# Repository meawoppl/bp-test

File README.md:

# PCB workspace

Choose a board in the portal using the selector configured in [`.kicad-pcb.json`](.kicad-pcb.json).

**Moved out (2026-10-20):**

- The ESP32 + iCE40 "gumstick" module (v1 DF40 module, v2 M.2 draft) and its
  programming carrier now live in **[OrbitalCommons/gumstick](https://github.com/OrbitalCommons/gumstick)**
  (public, history preserved; v1 ordered files under Git tag `v1`). Start with the
  [v1 ICD](https://github.com/OrbitalCommons/gumstick/blob/main/current-df40-connectors/docs/ICD-v1.md).
  It is included here as the submodule `third_party/gumstick`
  (`git submodule update --init`) because the Tesla controller scripts read the carrier.
- The GPS time calibrator, now named **StratumZero** (board, case, firmware,
  gateware, validation plan), lives in **[OrbitalCommons/stratumzero](https://github.com/OrbitalCommons/stratumzero)**
  (private for now).

Boards here:

- [Tesla coil controller](boards/tesla-coil-controller/README.md).
- [Original MainBoard](boards/mainboard-reference): native KiCad import for reference; original Fusion/Eagle exports in [source/fusion](source/fusion).
- Direction LED tester: existing board and fabrication files described below.

# Direction LED Differential Input Test Board

A compact 5 V BNC polarity indicator and Backplane workflow test project.

## Revision C

The schematic, 32 × 20 mm PCB, and fabrication files now match. The board is
73% smaller than the original 75 × 32 mm layout. The BNC body sits at the
left edge with its barrel overhanging, and the two indicators sit together on
the right. All routing is on top copper, with no vias.

- D1 / `+` (green 1206) lights when the BNC center is positive relative to its shell.
- D2 / `-` (red 1206) lights when the center is negative relative to its shell.
- A shared 1 kOhm 0805 resistor feeds directly antiparallel LEDs, limiting current
  and allowing the conducting LED to limit reverse voltage across the other.

There are four components: J1, R1, D1, and D2. R2 is removed.

[Layout drawing](docs/layout-review.svg) · [3D view](docs/layout-3d.png) ·
[Schematic](docs/schematic-review.svg)

## Verification and ordering

KiCad 10.0.6 ERC: **0 violations**. DRC with schematic parity: **0 violations,
0 unconnected items, 0 parity issues**, under the current project settings.
Gerbers, drills, BOM, and placements have been regenerated for revision C.

The package is ready for fabrication/assembly review, not an already approved
order. Confirm JLCPCB stock, through-hole assembly of J1, and LED rotation in
the assembly preview. No physical prototype has been tested. See the
[manufacturing notes](docs/manufacturing-notes.md) and [fabrication package](fab/README.md).

## Project files

| File or directory | Purpose |
| --- | --- |
| `direction-led-tester.kicad_pro` | KiCad project settings |
| `direction-led-tester.kicad_sch` | Revision C schematic |
| `direction-led-tester.kicad_pcb` | Revision C, 32 × 20 mm board |
| `bp-test.kicad_sym` | Vendored KiCad resistor and LED symbols |
| `fp-lib-table`, `sym-lib-table` | Project-local library mappings |
| `Resistor_SMD.pretty/`, `LED_SMD.pretty/` | Local KiCad footprints |
| `3dmodels/` | Resistor and LED STEP models |
| `lcsc/` | BNC symbol, corrected footprint, and STEP/WRL source models |
| `fab/` | Revision C fabrication, assembly, and check outputs |

The [workflow log](docs/plugin-workflow-log.md) records plugin testing and prior
revisions; use the current manufacturing notes for ordering requirements.

## Tesla coil controller

[Acquisition-first controller development](boards/tesla-coil-controller/README.md): eight simultaneous ADC channels, module v1 carrier interface, and two routed UD2.7-derived GDT bridges. This is an unfinished development board, not a fabrication release.

## License

[MIT](LICENSE). Third-party datasheets, vendor 3D models and imported library
files included for reference keep their own terms; see
`NOTICE`.

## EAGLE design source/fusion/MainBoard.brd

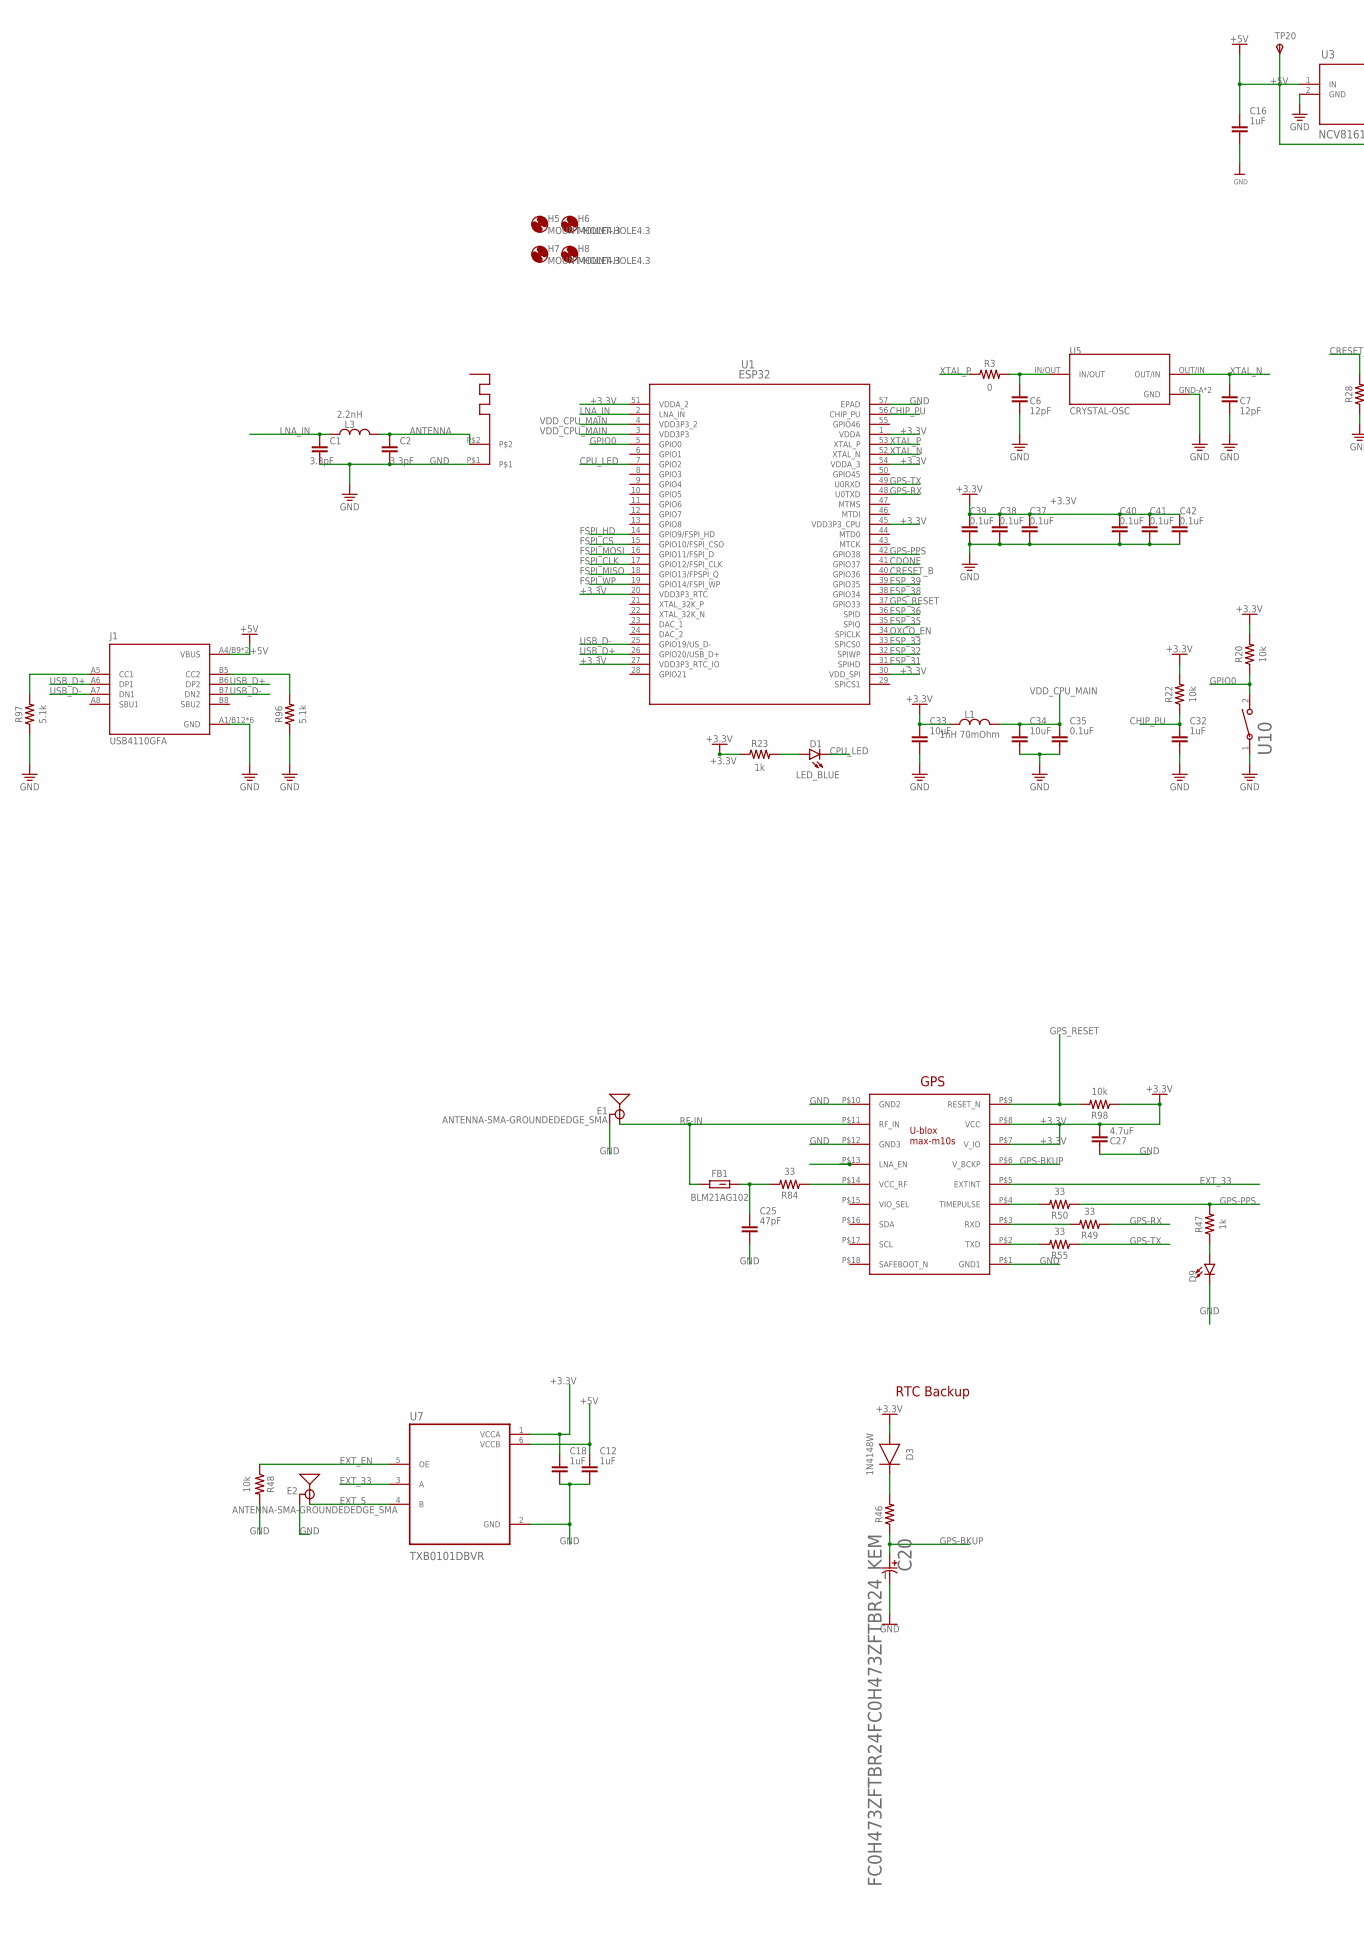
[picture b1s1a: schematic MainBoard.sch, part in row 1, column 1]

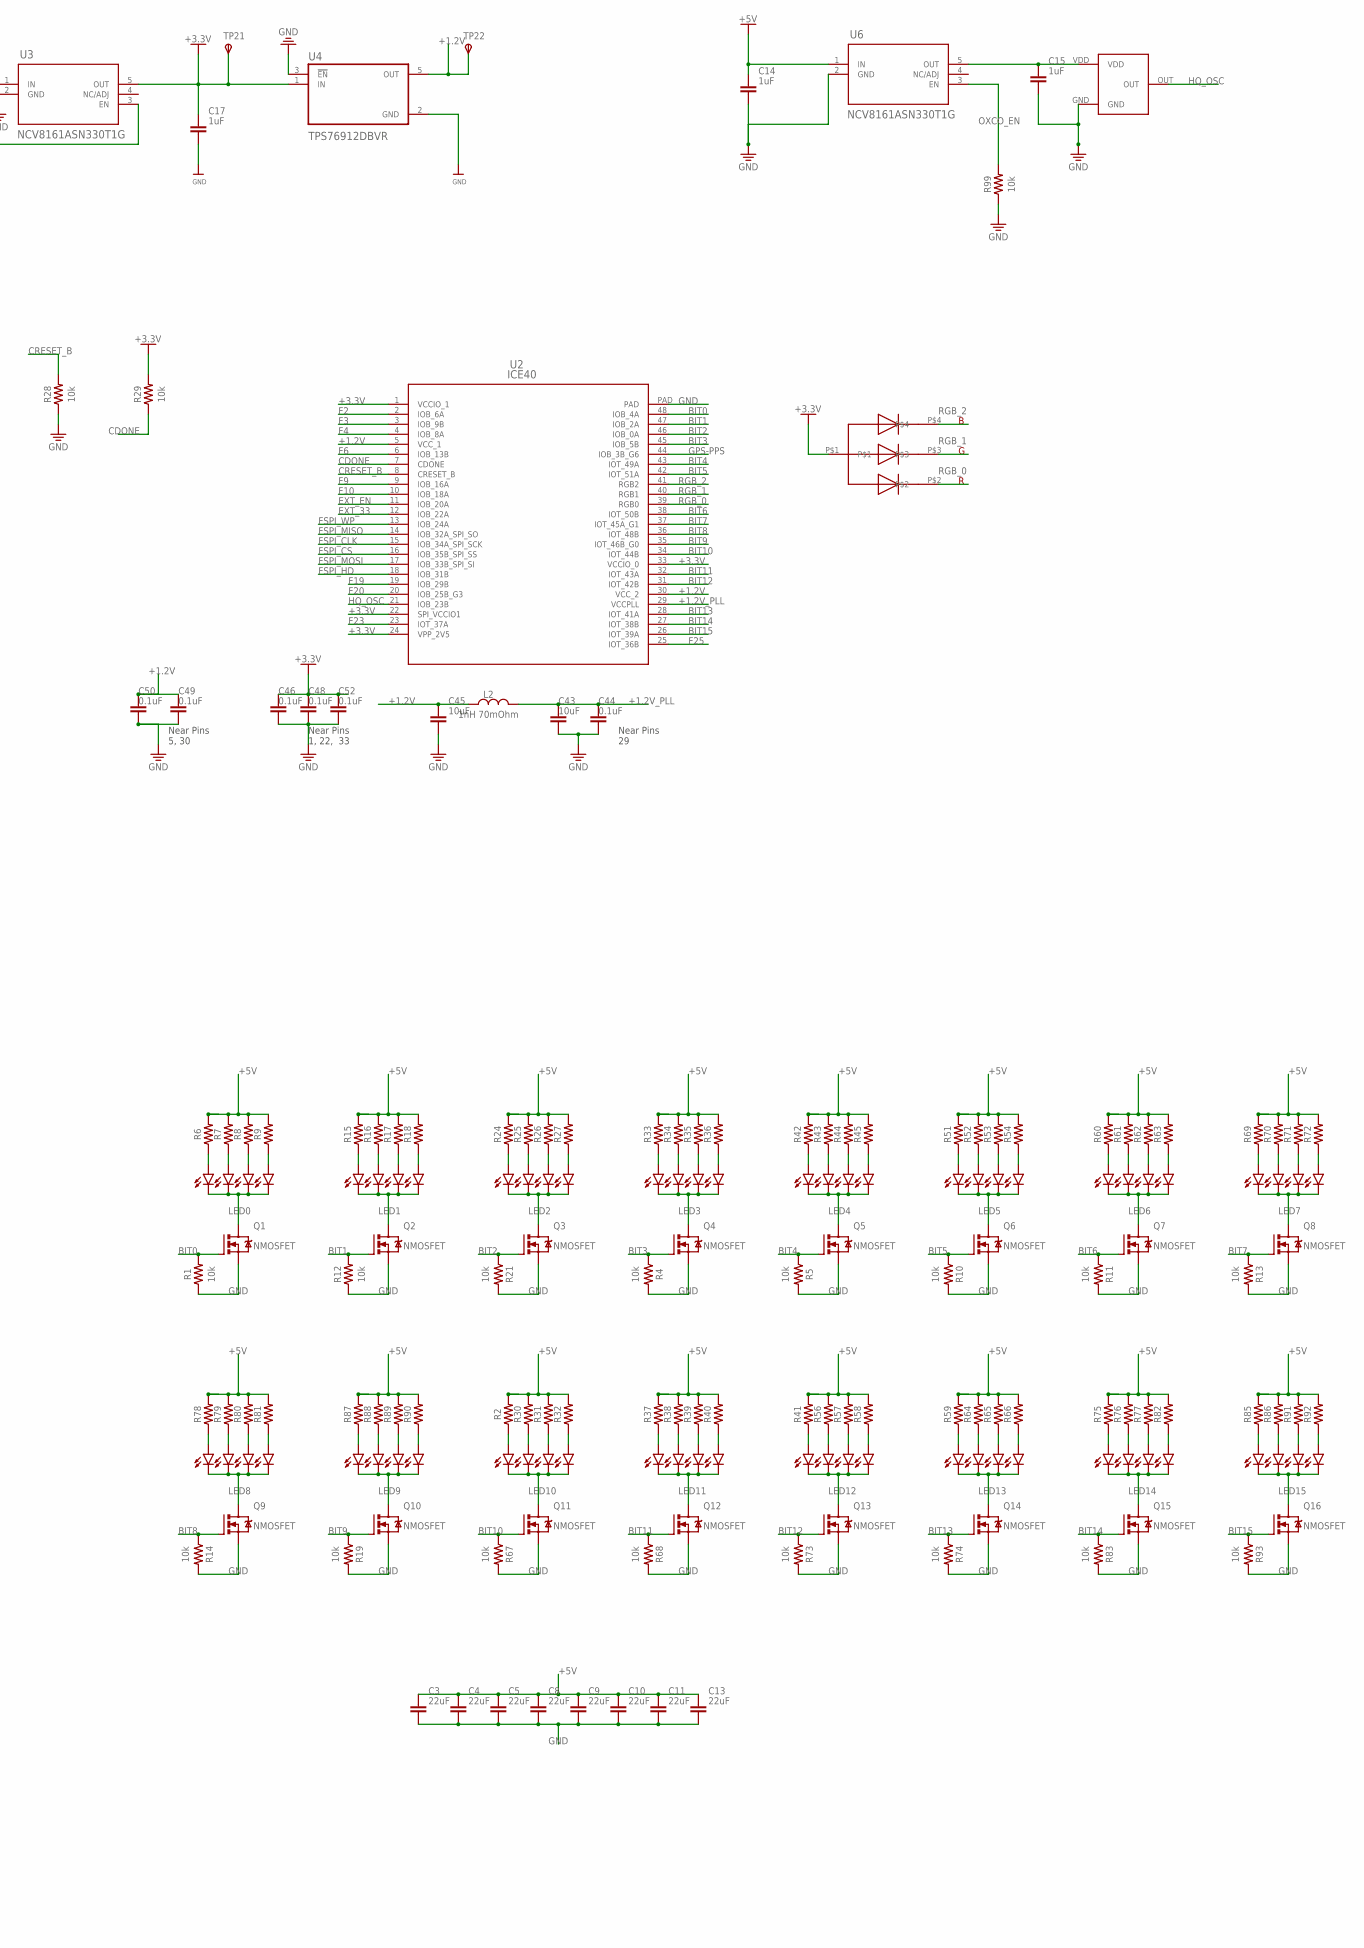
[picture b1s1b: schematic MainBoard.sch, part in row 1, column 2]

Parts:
C1, C2: 3.3pF; CAPC1005X60; LCSC_PART C76906
C3, C4, C5, C8, C9, C10, C11, C13: 22uF; CAPC3225X135; LCSC_PART C52306
C6, C7: 12pF; CAPC1005X60; LCSC_PART C26406
C12, C18, C32: 1uF; CAPC1005X60; LCSC_PART C29266
C14, C15, C16, C17: 1uF; CAPC2012X110; LCSC C28323
C20: FC0H473ZFTBR24FC0H473ZFTBR24_KEM; FC0H473ZFTBR24_KEM
C25: 47pF; CAPC1005X60; LCSC_PART C1671
C27: 4.7uF; CAPC1005X60; LCSC_PART C23733
C33, C34, C43, C45: 10uF; CAPC1005X60; LCSC_PART C76991
C35, C37, C38, C39, C40, C41, C42, C44, C46, C48, C49, C50, C52: 0.1uF; CAPC1005X60; LCSC_PART C1525
D1: LED_BLUE; LEDC1005X25N_FLAT-B; LCSC_PART C22355736
D2, D5, D6, D7, D8, D10, D11, D12, D13, D14, D15, D16, D17, D18, D19, D20, D21, D22, D23, D24, D25, D26, D27, D28, D29, D30, D31, D32, D33, D34, D35, D36, D37, D38, D39, D40, D41, D42, D43, D44, D45, D46, D47, D48, D49, D50, D51, D52, D53, D54, D55, D60, D61, D62, D63, D68, D69, D70, D71, D76, D77, D78, D79: LED_BLUE; LEDC3216X180N_RND-B
D3: 1N4148W; SOD3715X135; LCSC_PART C2128
D4: LED_BLUE; LEDC3216X180N_RND-B; LCSC_PART C375482
D9: LED0603; LED-0603; LCSC_PART C2286
E1, E2: ANTENNA-SMA-GROUNDEDEDGE_SMA; SMA-EDGE
FB1: BLM21AG102; BEADC2012X105N; LCSC_PART C76817
H5, H6, H7, H8: MOUNT-HOLE4.3; 4,3
J1: USB4110GFA; GCT_USB4110GFA; LCSC_PART C34260841
L1, L2: 1nH 70mOhm; INDC1006X60N; LCSC_PART C18222
L3: 2.2nH; INDC1006X60N; LCSC_PART C86061
Q1, Q2, Q3, Q4, Q5, Q6, Q7, Q8, Q9, Q10, Q11, Q12, Q13, Q14, Q15, Q16: NMOSFET; SOT23; LCSC_PART C478010
R1, R4, R5, R10, R11, R12, R13, R14, R19, R21, R67, R68, R73, R74, R83, R93: 10k; RESC2012X65; LCSC_PART C60490
R2, R6, R7, R8, R9, R15, R16, R17, R18, R24, R25, R26, R27, R30, R31, R32, R33, R34, R35, R36, R37, R38, R39, R40, R41, R42, R43, R44, R45, R46, R51, R52, R53, R54, R56, R57, R58, R59, R60, R61, R62, R63, R64, R65, R66, R69, R70, R71, R72, R75, R76, R77, R78, R79, R80, R81, R82, R85, R86, R87, R88, R89, R90, R91, R92: R-US_CHIP-0805(2012-METRIC); RESC2012X65
R3: 0; RESC1005X40; LCSC_PART C17168
R20, R22, R28, R29, R48, R98, R99: 10k; RESC1005X40; LCSC_PART C60490
R23, R47: 1k; RESC1005X40; LCSC_PART C11702
R49, R50, R55, R84: 33; RESC1005X40; LCSC_PART C25105
R96, R97: 5.1k; RESC1005X40; LCSC_PART C25905
TP20, TP22: TPSB1,27; B1,27
TP21: TPSB1,27; B1,27; LCSC DNP
U1: ESP32; QFN56_ESP32-S2FH4_EXP-M
U2: ICE40; ICE40-QFN
U3, U6: NCV8161ASN330T1G; TSOP5_3X1P5_ONS-M
U4: TPS76912DBVR
U5: CRYSTAL-OSC; XTAL_ECS-400-10-36-CKY-TR
U7: TXB0101DBVR; SOT95P280X145-6N; LCSC C2652944
U9: RGBLED
U10: TS-1185-C-A-A-A; SW_CS1213AGF260_CRS
U11: MAX-M10S-00B
U$1: PCB-ANTENNA
U$2: ACO97

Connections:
+1.2V: C45.1, C49.1, C50.1, L2.1, TP22.TP, U2.5 (VCC_1), U2.30 (VCC_2), U4.5 (OUT)
+1.2V_PLL: C43.1, C44.1, L2.2, U2.29 (VCCPLL)
+3.3V: C17.1, C18.1, C27.1, C33.1, C37.1, C38.1, C39.1, C40.1, C41.1, C42.1, C46.1, C48.1, C52.1, D3.2 (A), L1.1, R20.2, R22.2, R23.1, R29.2, R98.1, TP21.TP, U1.1 (VDDA), U1.20 (VDD3P3_RTC), U1.27 (VDD3P3_RTC_IO), U1.30 (VDD_SPI), U1.45 (VDD3P3_CPU), U1.51 (VDDA_2), U1.54 (VDDA_3), U2.1 (VCCIO_1), U2.22 (SPI_VCCIO1), U2.24 (VPP_2V5), U2.33 (VCCIO_0), U3.5 (OUT), U4.1 (IN), U7.1 (VCCA), U9.P$1, U11.P$7 (V_IO), U11.P$8 (VCC)
+5V: C3.1, C4.1, C5.1, C8.1, C9.1, C10.1, C11.1, C12.1, C13.1, C14.1, C16.1, J1.A4/B9 (VBUS), J1.B4/A9 (VBUS), R2.2, R6.2, R7.2, R8.2, R9.2, R15.2, R16.2, R17.2, R18.2, R24.2, R25.2, R26.2, R27.2, R30.2, R31.2, R32.2, R33.2, R34.2, R35.2, R36.2, R37.2, R38.2, R39.2, R40.2, R41.2, R42.2, R43.2, R44.2, R45.2, R51.2, R52.2, R53.2, R54.2, R56.2, R57.2, R58.2, R59.2, R60.2, R61.2, R62.2, R63.2, R64.2, R65.2, R66.2, R69.2, R70.2, R71.2, R72.2, R75.2, R76.2, R77.2, R78.2, R79.2, R80.2, R81.2, R82.2, R85.2, R86.2, R87.2, R88.2, R89.2, R90.2, R91.2, R92.2, TP20.TP, U3.1 (IN), U3.3 (EN), U6.1 (IN), U7.6 (VCCB)
ANTENNA: C2.1, L3.2, U$1.P$2
BIT0: Q1.1 (G), R1.2, U2.48 (IOB_4A)
BIT1: Q2.1 (G), R12.2, U2.47 (IOB_2A)
BIT2: Q3.1 (G), R21.1, U2.46 (IOB_0A)
BIT3: Q4.1 (G), R4.1, U2.45 (IOB_5B)
BIT4: Q5.1 (G), R5.1, U2.43 (IOT_49A)
BIT5: Q6.1 (G), R10.1, U2.42 (IOT_51A)
BIT6: Q7.1 (G), R11.1, U2.38 (IOT_50B)
BIT7: Q8.1 (G), R13.1, U2.37 (IOT_45A_G1)
BIT8: Q9.1 (G), R14.1, U2.36 (IOT_48B)
BIT9: Q10.1 (G), R19.1, U2.35 (IOT_46B_G0)
BIT10: Q11.1 (G), R67.1, U2.34 (IOT_44B)
BIT11: Q12.1 (G), R68.1, U2.32 (IOT_43A)
BIT12: Q13.1 (G), R73.1, U2.31 (IOT_42B)
BIT13: Q14.1 (G), R74.1, U2.28 (IOT_41A)
BIT14: Q15.1 (G), R83.1, U2.27 (IOT_38B)
BIT15: Q16.1 (G), R93.1, U2.26 (IOT_39A)
CDONE: R29.1, U1.41 (GPIO37), U2.7 (CDONE)
CHIP_PU: C32.1, R22.1, U1.56 (CHIP_PU)
CPU_LED: D1.C, U1.7 (GPIO2)
CRESET_B: R28.2, U1.40 (GPIO36), U2.8 (CRESET_B)
ESP_31: U1.31 (SPIHD)
ESP_32: U1.32 (SPIWP)
ESP_33: U1.33 (SPICS0)
ESP_35: U1.35 (SPIQ)
ESP_36: U1.36 (SPID)
ESP_38: U1.38 (GPIO34)
ESP_39: U1.39 (GPIO35)
EXT_5: E2.SIG (SIGNAL), U7.4 (B)
EXT_33: U2.12 (IOB_22A), U7.3 (A), U11.P$5 (EXTINT)
EXT_EN: R48.1, U2.11 (IOB_20A), U7.5 (OE)
F2: U2.2 (IOB_6A)
F3: U2.3 (IOB_9B)
F4: U2.4 (IOB_8A)
F6: U2.6 (IOB_13B)
F9: U2.9 (IOB_16A)
F10: U2.10 (IOB_18A)
F19: U2.19 (IOB_29B)
F20: U2.20 (IOB_25B_G3)
F23: U2.23 (IOT_37A)
F25: U2.25 (IOT_36B)
FSPI_CLK: U1.17 (GPIO12/FSPI_CLK), U2.15 (IOB_34A_SPI_SCK)
FSPI_CS: U1.15 (GPIO10/FSPI_CSO), U2.16 (IOB_35B_SPI_SS)
FSPI_HD: U1.14 (GPIO9/FSPI_HD), U2.18 (IOB_31B)
FSPI_MISO: U1.18 (GPIO13/FPSPI_Q), U2.14 (IOB_32A_SPI_SO)
FSPI_MOSI: U1.16 (GPIO11/FSPI_D), U2.17 (IOB_33B_SPI_SI)
FSPI_WP: U1.19 (GPIO14/FSPI_WP), U2.13 (IOB_24A)
GND: C1.2, C2.2, C3.2, C4.2, C5.2, C6.2, C7.2, C8.2, C9.2, C10.2, C11.2, C12.2, C13.2, C14.2, C15.2, C16.2, C17.2, C18.2, C20.2, C25.2, C27.2, C32.2, C33.2, C34.2, C35.2, C37.2, C38.2, C39.2, C40.2, C41.2, C42.2, C43.2, C44.2, C45.2, C46.2, C48.2, C49.2, C50.2, C52.2, D9.C, E1.GND@0 (GND), E1.GND@1 (GND), E1.GND@2 (GND), E1.GND@3 (GND), E2.GND@0 (GND), E2.GND@1 (GND), E2.GND@2 (GND), E2.GND@3 (GND), J1.A1/B12 (GND), J1.B1/A12 (GND), J1.S1 (GND), J1.S2 (GND), J1.S3 (GND), J1.S4 (GND), Q1.2 (S), Q2.2 (S), Q3.2 (S), Q4.2 (S), Q5.2 (S), Q6.2 (S), Q7.2 (S), Q8.2 (S), Q9.2 (S), Q10.2 (S), Q11.2 (S), Q12.2 (S), Q13.2 (S), Q14.2 (S), Q15.2 (S), Q16.2 (S), R1.1, R4.2, R5.2, R10.2, R11.2, R12.1, R13.2, R14.2, R19.2, R21.2, R28.1, R48.2, R67.2, R68.2, R73.2, R74.2, R83.2, R93.2, R96.1, R97.1, R99.1, U1.57 (EPAD), U2.PAD, U3.2 (GND), U4.2 (GND), U4.3 (!EN), U5.GND-A (GND), U5.GND-B (GND), U6.2 (GND), U7.2 (GND), U10.1, U11.P$1 (GND1), U11.P$10 (GND2), U11.P$12 (GND3), U$1.P$1, U$2.GND
GPIO0: R20.1, U1.5 (GPIO0), U10.2
GPS-BKUP: C20.1, R46.1, U11.P$6 (V_BCKP)
GPS-PPS: R47.2, R50.1, U1.42 (GPIO38), U2.44 (IOB_3B_G6)
GPS-RX: R49.1, U1.48 (U0TXD)
GPS-TX: R55.1, U1.49 (U0RXD)
GPS_RESET: R98.2, U1.37 (GPIO33), U11.P$9 (RESET_N)
HQ_OSC: U2.21 (IOB_23B), U$2.OUT
LED0: D4.C, D5.C, D6.C, D7.C, Q1.3 (D)
LED1: D12.C, D13.C, D14.C, D15.C, Q2.3 (D)
LED2: D20.C, D21.C, D22.C, D23.C, Q3.3 (D)
LED3: D28.C, D29.C, D30.C, D31.C, Q4.3 (D)
LED4: D36.C, D37.C, D38.C, D39.C, Q5.3 (D)
LED5: D44.C, D45.C, D46.C, D47.C, Q6.3 (D)
LED6: D52.C, D53.C, D54.C, D55.C, Q7.3 (D)
LED7: D60.C, D61.C, D62.C, D63.C, Q8.3 (D)
LED8: D68.C, D69.C, D70.C, D71.C, Q9.3 (D)
LED9: D76.C, D77.C, D78.C, D79.C, Q10.3 (D)
LED10: D2.C, D8.C, D10.C, D11.C, Q11.3 (D)
LED11: D16.C, D17.C, D18.C, D19.C, Q12.3 (D)
LED12: D24.C, D25.C, D26.C, D27.C, Q13.3 (D)
LED13: D32.C, D33.C, D34.C, D35.C, Q14.3 (D)
LED14: D40.C, D41.C, D42.C, D43.C, Q15.3 (D)
LED15: D48.C, D49.C, D50.C, D51.C, Q16.3 (D)
LNA_IN: C1.1, L3.1, U1.2 (LNA_IN)
unnamed: D2.A, R2.1
unnamed: C6.1, R3.2, U5.IN/OUT
unnamed: D1.A, R23.2
unnamed: D8.A, R30.1
unnamed: D10.A, R31.1
unnamed: D11.A, R32.1
unnamed: D4.A, R6.1
unnamed: D5.A, R7.1
unnamed: D6.A, R8.1
unnamed: D7.A, R9.1
unnamed: D16.A, R37.1
unnamed: D17.A, R38.1
unnamed: D12.A, R15.1
unnamed: D13.A, R16.1
unnamed: D14.A, R17.1
unnamed: D15.A, R18.1
unnamed: D18.A, R39.1
unnamed: D19.A, R40.1
unnamed: D24.A, R41.1
unnamed: D25.A, R56.1
unnamed: D26.A, R57.1
unnamed: D20.A, R24.1
unnamed: D21.A, R25.1
unnamed: D22.A, R26.1
unnamed: D23.A, R27.1
unnamed: D27.A, R58.1
unnamed: D32.A, R59.1
unnamed: R84.1, U11.P$14 (VCC_RF)
unnamed: D28.A, R33.1
unnamed: D29.A, R34.1
unnamed: D30.A, R35.1
unnamed: D31.A, R36.1
unnamed: C25.1, FB1.2, R84.2
unnamed: D9.A, R47.1
unnamed: D3.1 (C), R46.2
unnamed: D33.A, R64.1
unnamed: D36.A, R42.1
unnamed: D37.A, R43.1
unnamed: D38.A, R44.1
unnamed: D39.A, R45.1
unnamed: R50.2, U11.P$4 (TIMEPULSE)
unnamed: R49.2, U11.P$3 (RXD)
unnamed: R55.2, U11.P$2 (TXD)
unnamed: D34.A, R65.1
unnamed: D35.A, R66.1
unnamed: D44.A, R51.1
unnamed: D45.A, R52.1
unnamed: D46.A, R53.1
unnamed: D47.A, R54.1
unnamed: D40.A, R75.1
unnamed: D41.A, R76.1
unnamed: D42.A, R77.1
unnamed: D43.A, R82.1
unnamed: J1.A5 (CC1), R97.2
unnamed: D52.A, R60.1
unnamed: D53.A, R61.1
unnamed: D54.A, R62.1
unnamed: D55.A, R63.1
unnamed: J1.B5 (CC2), R96.2
unnamed: C15.1, U6.5 (OUT), U$2.VDD
unnamed: D48.A, R85.1
unnamed: D60.A, R69.1
unnamed: D61.A, R70.1
unnamed: D62.A, R71.1
unnamed: D63.A, R72.1
unnamed: D49.A, R86.1
unnamed: D50.A, R91.1
unnamed: D51.A, R92.1
unnamed: D68.A, R78.1
unnamed: D69.A, R79.1
unnamed: D70.A, R80.1
unnamed: D71.A, R81.1
unnamed: D76.A, R87.1
unnamed: D77.A, R88.1
unnamed: D78.A, R89.1
unnamed: D79.A, R90.1
OXCO_EN: R99.2, U1.34 (SPICLK), U6.3 (EN)
RF-IN: E1.SIG (SIGNAL), FB1.1, U11.P$11 (RF_IN)
RGB_0: U2.39 (RGB0), U9.P$2
RGB_1: U2.40 (RGB1), U9.P$3
RGB_2: U2.41 (RGB2), U9.P$4
USB_D+: J1.A6 (DP1), J1.B6 (DP2), U1.26 (GPIO20/USB_D+)
USB_D-: J1.A7 (DN1), J1.B7 (DN2), U1.25 (GPIO19/US_D-)
VDD_CPU_MAIN: C34.1, C35.1, L1.2, U1.3 (VDD3P3), U1.4 (VDD3P3_2)
XTAL_N: C7.1, U1.52 (XTAL_N), U5.OUT/IN
XTAL_P: R3.1, U1.53 (XTAL_P)

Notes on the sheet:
Near Pins 1, 22, 33
Near Pins 29
Near Pins 5, 30
RTC Backup
GPS

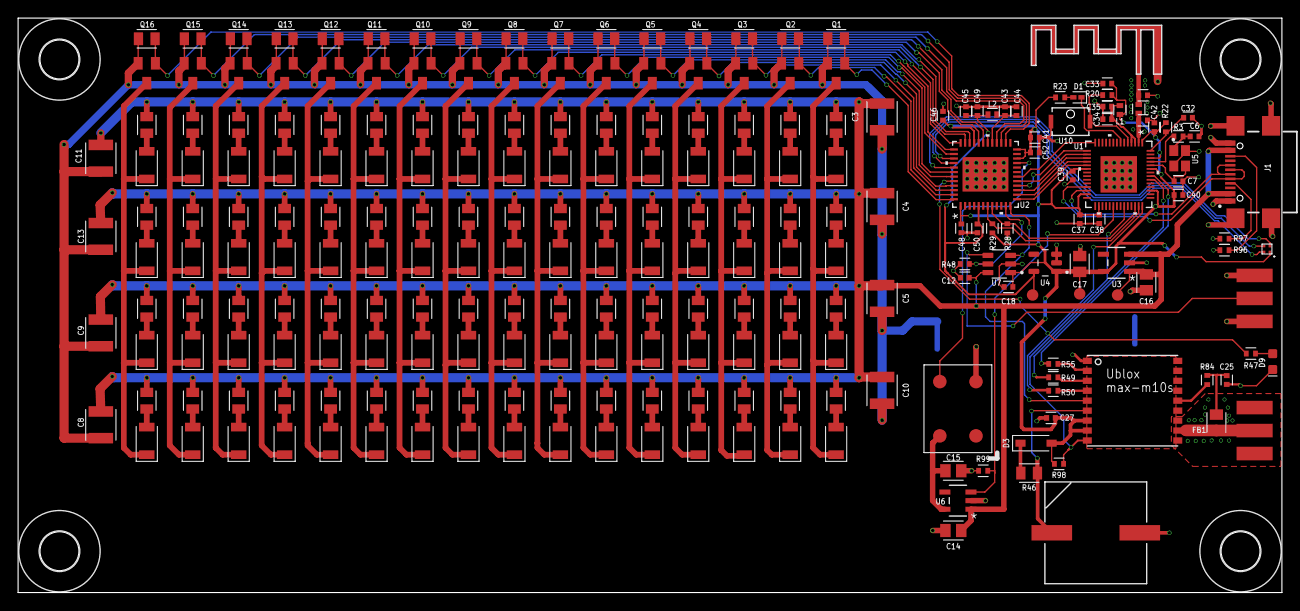
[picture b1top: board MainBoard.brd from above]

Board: 2 copper layers, 139.7 x 63.5 mm, 245 parts (0 on the bottom side), 145 nets.

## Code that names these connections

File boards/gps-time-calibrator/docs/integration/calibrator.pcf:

# GPS calibrator RFC v1 reference pin constraints. Port names must match NEW HDL.
# PCF does not supply clock/CDC constraints or implement safe reset behavior.
set_io FSPI_CLK 15
set_io FSPI_MOSI 17
set_io FSPI_MISO 14
set_io FSPI_CS 16
set_io OCXO_10M 44
set_io GPS_PPS 35
set_io TRIGGER_IN 38
set_io TRIGGER_OUT 42
set_io LED_OE_N 34
set_io LED_BITS[15] 10 # J2.2, FPGA_IOB_18A
set_io LED_BITS[14] 9 # J2.4, FPGA_IOB_16A
set_io LED_BITS[13] 12 # J2.5, FPGA_IOB_22A
set_io LED_BITS[12] 6 # J2.6, FPGA_IOB_13B
set_io LED_BITS[11] 11 # J2.7, FPGA_IOB_20A
set_io LED_BITS[10] 23 # J2.9, FPGA_IOT_37A
set_io LED_BITS[9] 21 # J2.10, FPGA_IOB_23B
set_io LED_BITS[8] 19 # J2.11, FPGA_IOB_29B
set_io LED_BITS[7] 20 # J2.12, FPGA_IOB_25B_G3
set_io LED_BITS[6] 25 # J2.14, FPGA_IOT_36B
set_io LED_BITS[5] 27 # J2.15, FPGA_IOT_38B
set_io LED_BITS[4] 26 # J2.16, FPGA_IOT_39A
set_io LED_BITS[3] 28 # J2.17, FPGA_IOT_41A
set_io LED_BITS[2] 31 # J2.19, FPGA_IOT_42B
set_io LED_BITS[1] 32 # J2.20, FPGA_IOT_43A
set_io LED_BITS[0] 36 # J2.21, FPGA_IOT_48B
# Optional onboard RGB ports, only if instantiated in HDL:
# set_io RGB0 39
# set_io RGB1 40
# set_io RGB2 41

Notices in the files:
parts and their libraries:
COPYRIGHT: Copyright (C) 2025 Ultra Librarian. All rights reserved.
microbuilder: This work is placed in the public domain, and may be freely used for commercial and non-commercial work with the following conditions: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
